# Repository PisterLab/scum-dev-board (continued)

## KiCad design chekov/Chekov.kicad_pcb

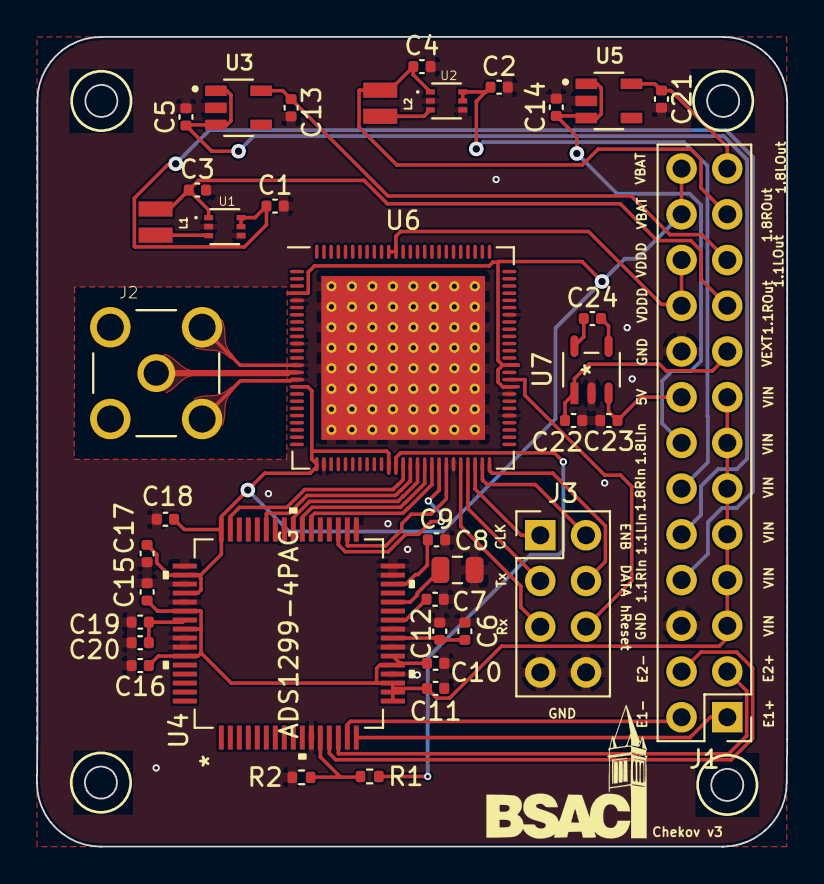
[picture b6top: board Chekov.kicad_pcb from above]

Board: 2 copper layers, 41.7 x 45.0 mm, 38 parts (0 on the bottom side), 43 nets.

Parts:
C1, C2, C3, C4: 10 uF; C_0402_1005Metric
C5, C7, C9, C10, C11, C13, C14, C15, C16, C17, C18, C20, C21: 1u; C_0402_1005Metric
C6, C23: 10u; C_0402_1005Metric
C8: 100u; C_0805_2012Metric
C12, C19, C24: 0.1u; C_0402_1005Metric
C22: 3.3u; C_0402_1005Metric
J1: Conn_02x13_Odd_Even; PinHeader_2x13_P2.54mm_Vertical
J2: CONSMA001-G-CONSMA001-G; LINX_CONSMA001-G
J3: Conn_02x04_Odd_Even; PinHeader_2x04_P2.54mm_Vertical
L1, L2: 2.2 uH; IND_74438343022
R1: 100k; R_0402_1005Metric
R2: 0.82; R_0402_1005Metric
U1: S-85S1AB10-I6T1U; SOFL50P180X50-6N
U2: S-85S1AB18-I6T1U; SOFL50P180X50-6N
U3: TLV70311DBVR; SOT95P280X145-5N
U4: ADS1299-4PAG
U5: TPS7A0518PDBVT; SOT95P280X145-5N
U6: scum3; QFN-100_EP_12x12_Pitch0.4mm_Margin0.25mm
U7: LTC1517ES5-5-TRPBF

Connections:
+VBAT: C17.1, C18.1, J1.24, J1.26, U4.48, U4.50, U4.52, U6.4, U6.17, U6.26, U6.36, U6.59, U6.62
+VDDD: J1.20, J1.22, U6.89, U6.90
+VEXT: C22.1, J1.17, U7.1
+VIN: C10.1, C11.1, C15.1, C16.1, J1.5, J1.7, J1.9, J1.11, J1.13, J1.15, U4.17, U4.18, U4.19, U4.21, U4.22, U4.54, U4.56, U4.59
/5V: C23.1, J1.16, U7.3
/Antenna: J2.1, U6.15
/CLK: J3.1, U6.48
/DATA: J3.4, U6.50
/E1Minus: J1.2, U4.15
/E1Plus: J1.1, U4.16
/E2Minus: J1.4, U4.13
/E2Plus: J1.3, U4.14
/ENB: J3.2, U6.49
/GPIO8: R1.2, U6.37
/GPIO9: U4.47, U6.38
/GPIO10: U4.43, U6.39
/GPIO11: U4.40, U6.40
/GPIO12: U4.39, U6.41
/GPIO13: U4.38, U6.42
/GPIO14: U4.35, U4.36, U6.43
/GPIO15: U4.34, U6.44
/LDO_In1.1: C5.1, J1.10, U3.1, U3.3
/LDO_In1.8: C14.1, J1.14, U5.1, U5.3
/LDO_Out1.1: C13.2, J1.21, U3.5
/LDO_Out1.8: C21.2, J1.25, U5.5
/Reg_In1.1: C1.1, J1.8, U1.5, U1.6
/Reg_In1.8: C2.1, J1.12, U2.5, U2.6
/Reg_Out1.1: C3.1, J1.19, L1.1, U1.1
/Reg_Out1.8: C4.1, J1.23, L2.1, U2.1
/RsRx: J3.5, U6.46
/RsTx: J3.3, U6.47
/hRESET: J3.6, U6.60
/uV: R1.1, R2.2, U4.12
GND: C1.2, C2.2, C3.2, C4.2, C5.2, C6.2, C7.1, C8.1, C9.1, C10.2, C11.2, C12.2, C13.1, C14.2, C15.2, C16.2, C17.2, C18.2, C19.2, C20.2, C21.1, C22.2, C23.2, J1.6, J1.18, J2.S1, J2.S2, J2.S3, J2.S4, J3.7, J3.8, R2.1, U1.2, U1.4, U2.2, U2.4, U3.2, U4.11, U4.20, U4.23, U4.25, U4.31, U4.32, U4.33, U4.41, U4.49, U4.51, U4.53, U4.57, U4.58, U5.2, U6.5, U6.11, U6.14, U6.16, U6.27, U6.45, U6.55, U6.58, U6.69, U6.101, U7.2
unnamed: C7.2, U4.26
unnamed: C8.2, U4.28
unnamed: C9.2, U4.30
unnamed: C6.1, C12.1, U4.24
unnamed: C19.1, C20.1, U4.55
unnamed: C24.1, U7.5
unnamed: C24.2, U7.4
unnamed: L1.2, U1.3
unnamed: L2.2, U2.3

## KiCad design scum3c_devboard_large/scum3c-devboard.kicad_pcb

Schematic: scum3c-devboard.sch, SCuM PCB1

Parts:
C1: 1.5 pF; C_0402_1005Metric
C3, C26, C27: 0.1uF; C_0402_1005Metric
C8, C9, C12, C23, C25, C28: 10 uF; C_0402_1005Metric
E1: 2450AT45A100E; ANT_2450AT45A100E; PARTREV 3.1
H1, H2, H3, H4: MountingHole; MountingHole_2.7mm_M2.5
J1: CONSMA001-G; LINX_CONSMA001-G; PARTREV D
J2: Conn_02x04_Odd_Even; PinHeader_2x04_P2.54mm_Vertical
J3: Conn_02x10_Odd_Even; PinHeader_2x10_P2.54mm_Vertical
J4: Conn_02x13_Odd_Even; PinHeader_2x13_P2.54mm_Vertical
L2, L3, L5: 2.2 uH; L_0402_1005Metric
L4: 3.9 nH; L_0402_1005Metric
U1: Perfboard
U5: ICM-20948; QFN40P300X300X105-24N; PARTREV 1.3
U6: S-85S1AB10-I6T1U; SOFL50P180X50-6N; PARTREV 1.4_00
U7: S-85S1AB15-I6T1U; SOFL50P180X50-6N; PARTREV 1.4_00
U12: S-85S1AB18-I6T1U; SOFL50P180X50-6N; PARTREV 1.4_00
U14, U15: 74AVCH4T245D,118; SOIC127P600X175-16N

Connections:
+1VIN: C25.1, J4.15, L2.1, U6.1 (VOUT)
+15VIN: C28.1, J4.9, L3.1, U7.1 (VOUT)
+TEENSY33: J4.2; also elsewhere on the board
+V18IO: C12.1, J2.7, J4.4, L5.1, U12.1 (VOUT), U14.1, U15.1, U15.2
+V18IO_IMU: C27.1, J2.8, U5.8 (VDDIO)
+VBAT: J4.8, J4.10, J4.11, J4.23; also elsewhere on the board
+VBATSCuM: J4.12; also elsewhere on the board
+VDDD: J4.16, J4.18, J4.19; also elsewhere on the board
+VDDIO: J4.6, J4.13, J4.21, U14.16, U15.16; also elsewhere on the board
+VDDIOSCuM: J4.14; also elsewhere on the board
+VIN: C8.1, C9.1, C23.1, J2.5, J4.1, J4.5, J4.25, U6.5 (VIN), U6.6 (EN), U7.5 (VIN), U7.6 (EN), U12.5 (VIN), U12.6 (EN); also elsewhere on the board
+VIN_IMU: C26.1, J2.6, U5.13 (VDD)
/ADC_IN: J2.3; also elsewhere on the board
/ADC_LDO_OUT: J2.4; also elsewhere on the board
/Boot_Source_Sel: J4.17; also elsewhere on the board
/GPIO0: J3.5; also elsewhere on the board
/GPIO1: J3.2, J3.4, J3.6; also elsewhere on the board
/GPIO2: J3.7; also elsewhere on the board
/GPIO3: J3.8; also elsewhere on the board
/GPIO4: J3.9; also elsewhere on the board
/GPIO5: J3.10; also elsewhere on the board
/GPIO6: J3.11; also elsewhere on the board
/GPIO7: J3.12; also elsewhere on the board
/GPIO8: J3.1, J3.13; also elsewhere on the board
/GPIO9: J3.3, J3.14; also elsewhere on the board
/GPIO10: J3.15; also elsewhere on the board
/GPIO11: J3.16; also elsewhere on the board
/GPIO12: J3.17, U14.11; also elsewhere on the board
/GPIO12_IMU: U5.24 (SDA/SDI), U14.6
/GPIO13: J3.18, U15.12; also elsewhere on the board
/GPIO13_IMU: U5.9 (AD0/SDO), U15.5
/GPIO14: J3.19, U14.12; also elsewhere on the board
/GPIO14_IMU: U5.23 (SCL/SCLK), U14.5
/GPIO15: J3.20, U14.10; also elsewhere on the board
/GPIO15_IMU: U5.22 (~CS), U14.7
/RF_IN: C1.2, J1.1; also elsewhere on the board
GND: C3.1, C8.2, C9.2, C12.2, C23.2, C25.2, C26.2, C27.2, C28.2, J1.S1, J1.S2, J1.S3, J1.S4, J2.1, J2.2, J4.7, J4.20, J4.22, J4.24, J4.26, L4.2, U5.11 (FSYNC), U5.18 (GND), U5.20 (RESV_20), U6.2 (VSS), U6.4 (PVSS), U7.2 (VSS), U7.4 (PVSS), U12.2 (VSS), U12.4 (PVSS), U14.2, U14.3, U14.8, U14.9, U14.14, U14.15, U15.3, U15.8, U15.9, U15.14, U15.15; also elsewhere on the board
unnamed: C1.1, E1.1, L4.1
unnamed: C3.2, U5.10 (REGOUT)
unnamed: L2.2, U6.3 (SW)
unnamed: L3.2, U7.3 (SW)
unnamed: L5.2, U12.3 (SW)
unnamed: U1.11, U1.21, U1.31, U1.41
unnamed: U1.12, U1.22, U1.32, U1.42
unnamed: U1.13, U1.23, U1.33, U1.43
unnamed: U1.14, U1.24, U1.34, U1.44
unnamed: U1.15, U1.25, U1.35, U1.45
unnamed: U1.16, U1.26, U1.36, U1.46
unnamed: U1.17, U1.27, U1.37, U1.47
unnamed: U1.18, U1.28, U1.38, U1.48

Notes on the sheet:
IMU
Perfboard and Mounting Holes
Power Flags
UART
SCuM
Antenna
Teensy Connectors
DC-DC Converters
GPIO
Voltage Pins
ADC/IMU Pins
IMU Level Shifters

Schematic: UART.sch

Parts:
C2: 10nF; C_0402_1005Metric
C4: 4.7uF; C_0402_1005Metric
C5, C6, C7: 0.1uF; C_0402_1005Metric
C10, C11: 47pF; C_0402_1005Metric
C13: C; C_0402_1005Metric
D1, D2: LED; LED_0402_1005Metric
J5: 1050170001; MOLEX_1050170001; PARTREV F
J9: Conn_02x03_Odd_Even; PinHeader_2x03_P2.54mm_Vertical
L1: HZ0805E601R-10; L_0805_2012Metric; Manufacturer_Part_Number HZ0805E601R-10
R1, R4: 270; R_0402_1005Metric
R2, R3: 27; R_0402_1005Metric
U2: FT231XS-U; SSOP-20_3.9x8.7mm_P0.635mm; Manufacturer_Part_Number FT231XS-U; Mouser Part Number 895-FT231XS-U
U3, U4: 74AVC1T45GS-Q100H; 74LVC1G3157GS132; Manufacturer_Part_Number 74AVC1T45GS,132; Mouser Part Number 771-74AVC1T45GS132

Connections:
+VBAT: U3.1 (VCCA); also elsewhere on the board
+VDDIO: U4.1 (VCCA), U4.5 (DIR); also elsewhere on the board
+VIN: U3.6 (VCCB), U4.6 (VCCB); also elsewhere on the board
+VUSB: C4.1, C7.1, L1.2, U2.15 (VCC)
/RsRx: U3.3 (A); also elsewhere on the board
/RsTx: U4.3 (A); also elsewhere on the board
/Rx33: J9.2; also elsewhere on the board
/Tx33: J9.1; also elsewhere on the board
/UART/D_N: C11.2, J5.2, R3.2
/UART/D_P: C10.1, J5.3, R2.1
/UART/RsRx33: J9.4, U3.4 (B)
/UART/RsRx33USB: J9.6, U2.20 (TXD)
/UART/RsTx33: J9.3, U4.4 (B)
/UART/RsTx33USB: J9.5, U2.4 (RXD)
GND: C2.2, C4.2, C5.2, C6.2, C7.2, C10.2, C11.1, C13.2, J5.5, U2.6 (GND_1), U2.16 (GND_2), U3.2 (GND), U3.5 (DIR), U4.2 (GND); also elsewhere on the board
unnamed: C2.1, J5.1, L1.1
unnamed: C13.1, J5.SH1, J5.SH2, J5.SH3, J5.SH4, J5.SH5, J5.SH6, J5.SH7, J5.SH8
unnamed: D1.1 (K), U2.10 (CBUS2)
unnamed: D1.2 (A), R1.2
unnamed: D2.1 (K), U2.17 (CBUS1)
unnamed: D2.2 (A), R4.2
unnamed: R2.2, U2.11 (USBDP)
unnamed: R3.1, U2.12 (USBDM)

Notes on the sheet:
USB to UART
USB
UART Level Shifters
Jumpers

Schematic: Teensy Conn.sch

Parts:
J6: Conn_01x24; PinSocket_1x24_P2.54mm_Vertical
U9, U10, U11, U13: 74AVCH4T245D,118; SOIC127P600X175-16N

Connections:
+TEENSY33: J6.3; also elsewhere on the board
+VBAT: U9.1, U10.1, U11.1, U13.1, U13.2; also elsewhere on the board
+VIN: U9.16, U10.16, U11.16, U13.16; also elsewhere on the board
/3WB_CLK: U11.6; also elsewhere on the board
/3WB_DATA: U11.4; also elsewhere on the board
/3WB_ENB: U11.5; also elsewhere on the board
/Clock: U10.6; also elsewhere on the board
/GPIO0: J6.11; also elsewhere on the board
/GPO_ZERO: U10.7; also elsewhere on the board
/Rx33: J6.5, J6.23; also elsewhere on the board
/Teensy Connections/3WB_CLK33: J6.8, U11.11
/Teensy Connections/3WB_DATA33: J6.10, U11.13
/Teensy Connections/3WB_ENB33: J6.9, U11.12
/Teensy Connections/Clock33: J6.13, U10.11
/Teensy Connections/GPO_ZERO33: J6.12, U10.10
/Teensy Connections/aLOAD33: J6.19, U9.12
/Teensy Connections/aPHI33: J6.18, U9.11
/Teensy Connections/aPHIb33: J6.14, U10.12
/Teensy Connections/aSCANIN33: J6.20, U9.13
/Teensy Connections/aSCANOUT33: J6.16, J6.21, U13.13
/Teensy Connections/aSCSEL33: J6.17, J6.22, U9.10
/Teensy Connections/hReset33: J6.7, U11.10
/Tx33: J6.4, J6.24; also elsewhere on the board
/aLOAD: U9.5; also elsewhere on the board
/aPHI: U9.6; also elsewhere on the board
/aPHIb: U10.5; also elsewhere on the board
/aSCANIN: U9.4; also elsewhere on the board
/aSCANOUT: U13.4; also elsewhere on the board
/aSCSEL: U9.7; also elsewhere on the board
/hReset: U11.7; also elsewhere on the board
GND: J6.6, J6.15, U9.2, U9.3, U9.8, U9.9, U9.14, U9.15, U10.2, U10.3, U10.8, U10.9, U10.14, U10.15, U11.2, U11.3, U11.8, U11.9, U11.14, U11.15, U13.3, U13.8, U13.9, U13.14, U13.15; also elsewhere on the board

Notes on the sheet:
Teensy/nRF Connector
Level Shifters

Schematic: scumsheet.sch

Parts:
U8: scum3; QFN-100_EP_12x12_Pitch0.4mm

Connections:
+VBATSCuM: U8.4 (VBAT), U8.17 (VBAT), U8.26 (VBAT), U8.59 (VBAT), U8.62 (VBAT); also elsewhere on the board
+VDDD: U8.89 (VDDD), U8.90 (VDDD); also elsewhere on the board
+VDDIOSCuM: U8.36 (VDDIO); also elsewhere on the board
/3WB_CLK: U8.48 (3WB_CLK); also elsewhere on the board
/3WB_DATA: U8.50 (3WB_DATA); also elsewhere on the board
/3WB_ENB: U8.49 (3WB_ENB); also elsewhere on the board
/ADC_IN: U8.54 (SENSOR_EXT_IN); also elsewhere on the board
/ADC_LDO_OUT: U8.53 (SENSOR_LDO_OUTPUT); also elsewhere on the board
/Boot_Source_Sel: U8.61 (BOOT_SOURCE_SELECT); also elsewhere on the board
/Clock: U8.56 (LF_CLK_EXT_IN); also elsewhere on the board
/GPIO0: U8.28 (GPIO0); also elsewhere on the board
/GPIO1: U8.29 (GPIO1); also elsewhere on the board
/GPIO2: U8.30 (GPIO2); also elsewhere on the board
/GPIO3: U8.31 (GPIO3); also elsewhere on the board
/GPIO4: U8.32 (GPIO4); also elsewhere on the board
/GPIO5: U8.33 (GPIO5); also elsewhere on the board
/GPIO6: U8.34 (GPIO6); also elsewhere on the board
/GPIO7: U8.35 (GPIO7); also elsewhere on the board
/GPIO8: U8.37 (GPIO8); also elsewhere on the board
/GPIO9: U8.38 (GPIO9); also elsewhere on the board
/GPIO10: U8.39 (GPIO10); also elsewhere on the board
/GPIO11: U8.40 (GPIO11); also elsewhere on the board
/GPIO12: U8.41 (GPIO12); also elsewhere on the board
/GPIO13: U8.42 (GPIO13); also elsewhere on the board
/GPIO14: U8.43 (GPIO14); also elsewhere on the board
/GPIO15: U8.44 (GPIO15); also elsewhere on the board
/GPO_ZERO: U8.57 (GPO_ZERO); also elsewhere on the board
/RF_IN: U8.15 (RF_IN); also elsewhere on the board
/RsRx: U8.47 (RSRX); also elsewhere on the board
/RsTx: U8.46 (RSTX); also elsewhere on the board
/aLOAD: U8.66 (ASC_LOAD); also elsewhere on the board
/aPHI: U8.64 (ASC_PHI1); also elsewhere on the board
/aPHIb: U8.63 (ASC_PHI2); also elsewhere on the board
/aSCANIN: U8.67 (ASC_IN); also elsewhere on the board
/aSCANOUT: U8.65 (ASC_OUT); also elsewhere on the board
/aSCSEL: U8.68 (ASC_EXT_OVERRIDE); also elsewhere on the board
/hReset: U8.60 (HARD_RESET); also elsewhere on the board
GND: U8.5 (GND), U8.11 (GND), U8.14 (RF_GND), U8.16 (RF_GND), U8.27 (GND), U8.45 (GND), U8.55 (GND), U8.58 (GND), U8.69 (GND), U8.101 (GND); also elsewhere on the board

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
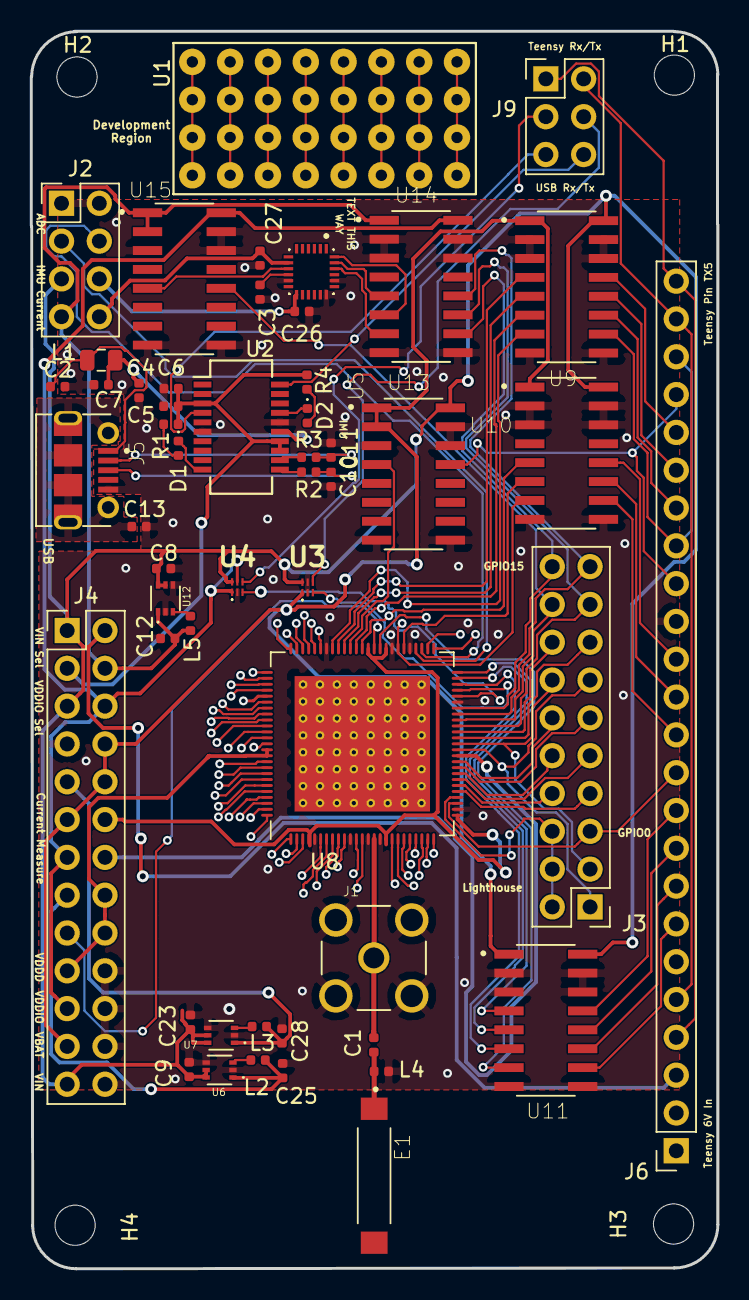
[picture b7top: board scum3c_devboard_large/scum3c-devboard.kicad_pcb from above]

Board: 2 copper layers, 46.1 x 83.1 mm, 56 parts (0 on the bottom side), 94 nets.

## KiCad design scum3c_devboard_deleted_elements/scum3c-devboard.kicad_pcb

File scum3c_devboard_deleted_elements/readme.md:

### Updates 2020.12.05
- removed zener diode
- added GPIOs 8, 9, 10
- added ground connections near GPIO
- added labels
- moved passives around
- added ADC pins

### Updates 2020.12.02
- Replaced antenna header with VDDD
- Kept LED
- 0-80 standoffs
- 0.1” -> 0.05” headers
- Removed GPIO 8-15 pins

### Updates 2020.10.07
- 30mm x 30 mm
- holes for standoffs
- SR521SW battery clip
- IMU
- GPIO, 3WB, UART, VBAT, VDDIO pins
- 1.8 V Zener diode for voltage protection
- LED programming indicator

### Updates 2021.01.15
- Added missing BOOT_SOURCE_SEL header

## useful specs
Use 0-80 standoffs. 1.6 mm diameter hole, 3.2 mm diameter clearance. https://www.4pcb.com/pcb-design-specifications/

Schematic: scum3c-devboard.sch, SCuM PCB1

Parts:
BT1: Battery_Cell; 2986
C25, C26, C27: 0.1uF; C_0402_1005Metric
J1: Conn_02x04_Odd_Even; PinHeader_2x04_P2.54mm_Vertical
J2, J5: Conn_01x02; PinHeader_1x02_P2.54mm_Vertical
J3: Conn_02x10_Odd_Even; PinHeader_2x10_P2.54mm_Vertical
J4: Conn_02x08_Odd_Even; PinHeader_2x08_P2.54mm_Vertical
JC1: Conn_01x01; PinHeader_1x01_P2.54mm_Vertical
U9AB1: ICM-20948; InvenSense_QFN-24_3x3mm_P0.4mm

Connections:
+VBAT: BT1.1 (+), J1.5, J4.1; also elsewhere on the board
+VDDD: J4.5, J4.7; also elsewhere on the board
+VDDIO: J1.1, J1.3, J1.6, J4.3; also elsewhere on the board
/3WB_CLK: J4.14; also elsewhere on the board
/3WB_DATA: J4.10; also elsewhere on the board
/3WB_ENB: J4.12; also elsewhere on the board
/ANTENNA: JC1.1; also elsewhere on the board
/BOOT_SOURCE_SEL: J4.8; also elsewhere on the board
/GPIO0: J3.1; also elsewhere on the board
/GPIO1: J2.1, J2.2, J3.3; also elsewhere on the board
/GPIO2: J3.5; also elsewhere on the board
/GPIO3: J3.7; also elsewhere on the board
/GPIO4: J3.9; also elsewhere on the board
/GPIO5: J3.11; also elsewhere on the board
/GPIO6: J3.13; also elsewhere on the board
/GPIO7: J3.15; also elsewhere on the board
/GPIO8: J3.2; also elsewhere on the board
/GPIO9: J3.4; also elsewhere on the board
/GPIO10: J3.6; also elsewhere on the board
/GPIO11: J3.8; also elsewhere on the board
/GPIO12: J3.10, U9AB1.24 (SDA/SDI); also elsewhere on the board
/GPIO13: J3.12, U9AB1.9 (SDO/AD0); also elsewhere on the board
/GPIO14: J3.14, U9AB1.23 (SCL/SCLK); also elsewhere on the board
/GPIO15: J3.16, U9AB1.22 (~CS); also elsewhere on the board
/GPO_ZERO: J5.2; also elsewhere on the board
/HARD_RESET: J4.16; also elsewhere on the board
/IMU_VDD: C26.1, J1.2, U9AB1.13 (VDD)
/IMU_VDDIO: C27.1, J1.4, U9AB1.8 (VDDIO)
/RsRx: J4.13; also elsewhere on the board
/RsTx: J4.15; also elsewhere on the board
/SENSOR_EXT_IN: J4.9; also elsewhere on the board
/SENSOR_LDO_OUTPUT: J4.11; also elsewhere on the board
GND: BT1.2 (-), C25.2, C26.2, C27.2, J1.7, J1.8, J3.17, J3.18, J3.19, J3.20, J4.2, J4.4, J4.6, J5.1, U9AB1.11 (FSYNC), U9AB1.18 (GND), U9AB1.20 (GND); also elsewhere on the board
unnamed: C25.1, U9AB1.10 (REGOUT)

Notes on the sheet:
Invensense MPU-9250 and ICM-20948 are pin compatible When using MPU-9250, VDDIO can be 1.71V-3.3V When using ICM-20948, VDDIO can be 1.71V-1.95V Easiest way to use ICM-20948 is to replace 1.5V VBAT LDO with 1.8V and set VDDIO=VBAT
SCuM
IMU
External Connections
Battery
McCoy PCB v1.1

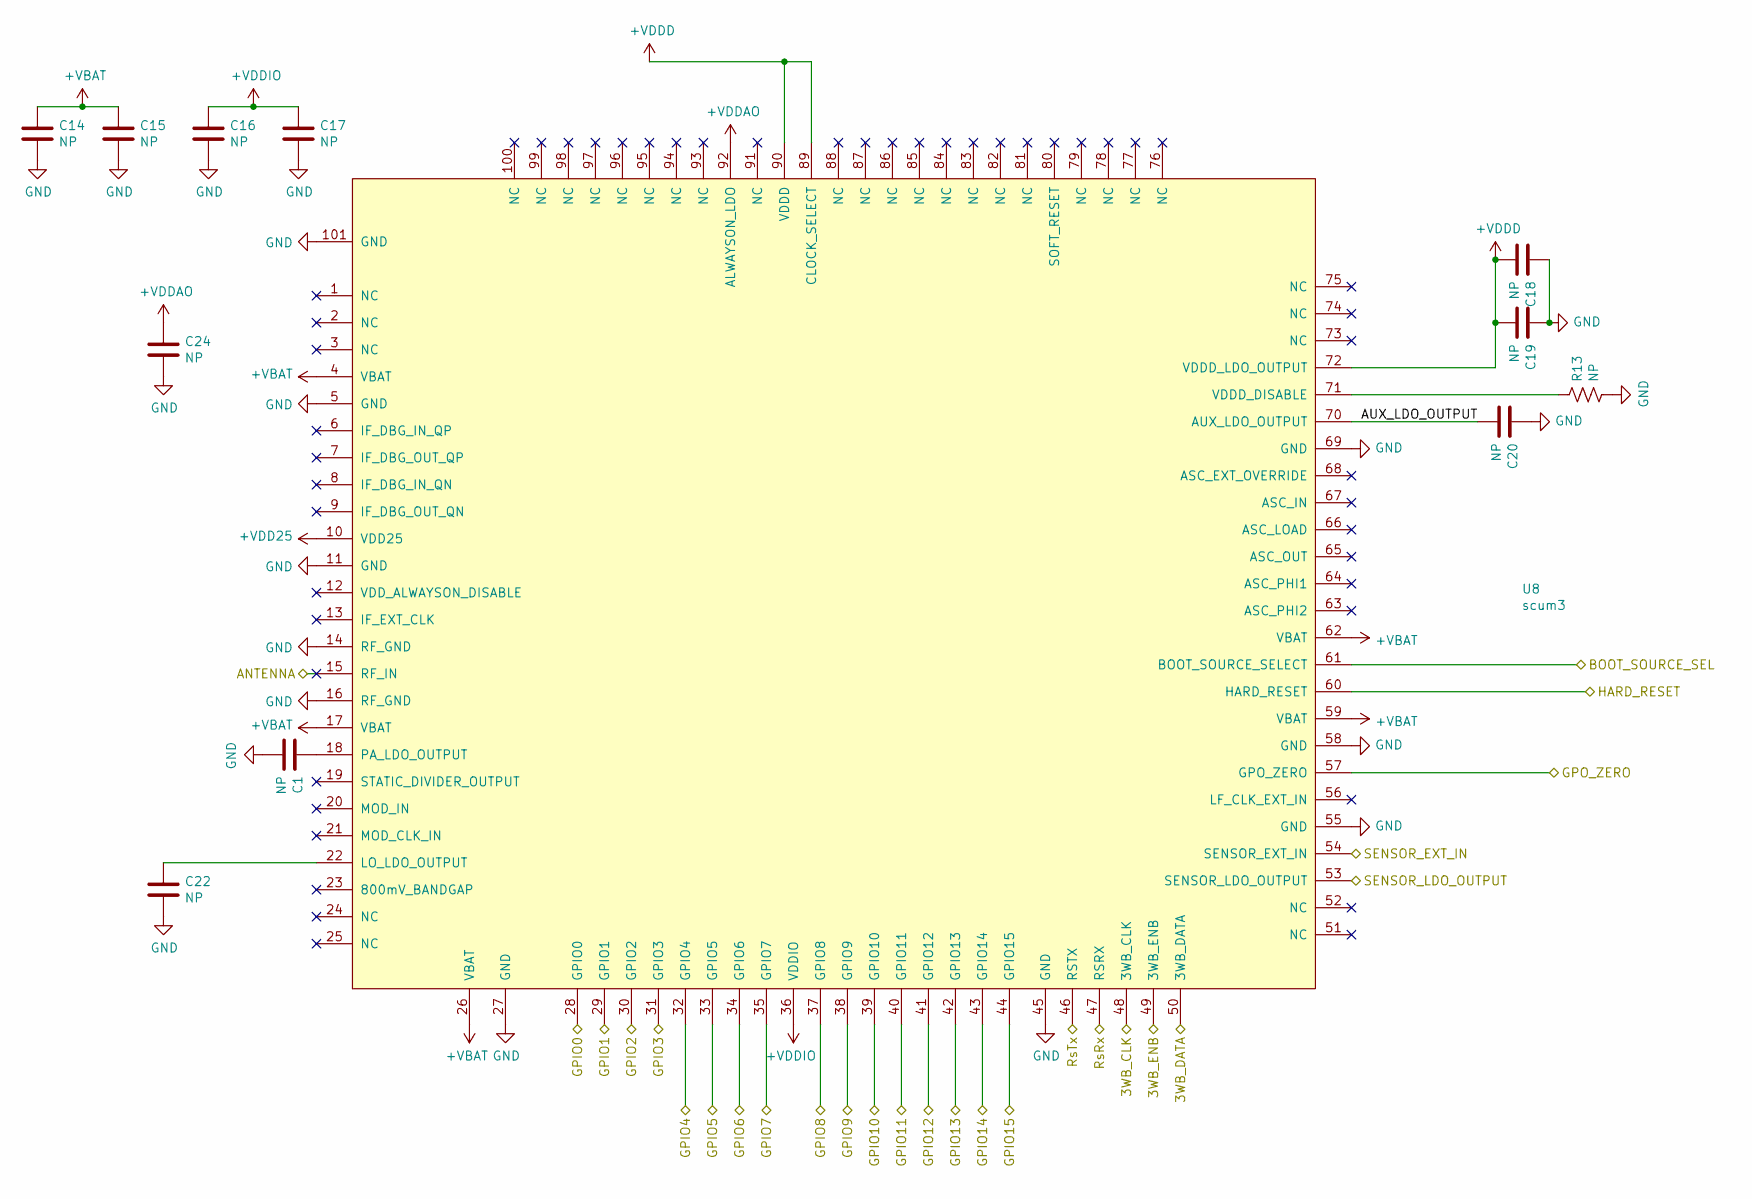
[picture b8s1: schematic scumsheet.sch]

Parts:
C1, C14, C15, C16, C17, C18, C19, C20, C22, C24: NP; C_0402_1005Metric
R13: NP; R_0402_1005Metric
U8: scum3; QFN-100_EP_12x12_Pitch0.4mm_Margin0.25mm

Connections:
+VBAT: C14.1, C15.1, U8.4 (VBAT), U8.17 (VBAT), U8.26 (VBAT), U8.59 (VBAT), U8.62 (VBAT); also elsewhere on the board
+VDDAO: C24.1, U8.92 (ALWAYSON_LDO)
+VDDD: C18.2, C19.2, U8.72 (VDDD_LDO_OUTPUT), U8.89 (CLOCK_SELECT), U8.90 (VDDD); also elsewhere on the board
+VDDIO: C16.1, C17.1, U8.36 (VDDIO); also elsewhere on the board
/3WB_CLK: U8.48 (3WB_CLK); also elsewhere on the board
/3WB_DATA: U8.50 (3WB_DATA); also elsewhere on the board
/3WB_ENB: U8.49 (3WB_ENB); also elsewhere on the board
/ANTENNA: U8.15 (RF_IN); also elsewhere on the board
/BOOT_SOURCE_SEL: U8.61 (BOOT_SOURCE_SELECT); also elsewhere on the board
/GPIO0: U8.28 (GPIO0); also elsewhere on the board
/GPIO1: U8.29 (GPIO1); also elsewhere on the board
/GPIO2: U8.30 (GPIO2); also elsewhere on the board
/GPIO3: U8.31 (GPIO3); also elsewhere on the board
/GPIO4: U8.32 (GPIO4); also elsewhere on the board
/GPIO5: U8.33 (GPIO5); also elsewhere on the board
/GPIO6: U8.34 (GPIO6); also elsewhere on the board
/GPIO7: U8.35 (GPIO7); also elsewhere on the board
/GPIO8: U8.37 (GPIO8); also elsewhere on the board
/GPIO9: U8.38 (GPIO9); also elsewhere on the board
/GPIO10: U8.39 (GPIO10); also elsewhere on the board
/GPIO11: U8.40 (GPIO11); also elsewhere on the board
/GPIO12: U8.41 (GPIO12); also elsewhere on the board
/GPIO13: U8.42 (GPIO13); also elsewhere on the board
/GPIO14: U8.43 (GPIO14); also elsewhere on the board
/GPIO15: U8.44 (GPIO15); also elsewhere on the board
/GPO_ZERO: U8.57 (GPO_ZERO); also elsewhere on the board
/HARD_RESET: U8.60 (HARD_RESET); also elsewhere on the board
/RsRx: U8.47 (RSRX); also elsewhere on the board
/RsTx: U8.46 (RSTX); also elsewhere on the board
/SENSOR_EXT_IN: U8.54 (SENSOR_EXT_IN); also elsewhere on the board
/SENSOR_LDO_OUTPUT: U8.53 (SENSOR_LDO_OUTPUT); also elsewhere on the board
/scumsheet/AUX_LDO_OUTPUT: C20.2, U8.70 (AUX_LDO_OUTPUT)
GND: C1.2, C14.2, C15.2, C16.2, C17.2, C18.1, C19.1, C20.1, C22.2, C24.2, R13.2, U8.5 (GND), U8.11 (GND), U8.14 (RF_GND), U8.16 (RF_GND), U8.27 (GND), U8.45 (GND), U8.55 (GND), U8.58 (GND), U8.69 (GND), U8.101 (GND); also elsewhere on the board
unnamed: C1.1, U8.18 (PA_LDO_OUTPUT)
unnamed: C22.1, U8.22 (LO_LDO_OUTPUT)
unnamed: R13.1, U8.71 (VDDD_DISABLE)

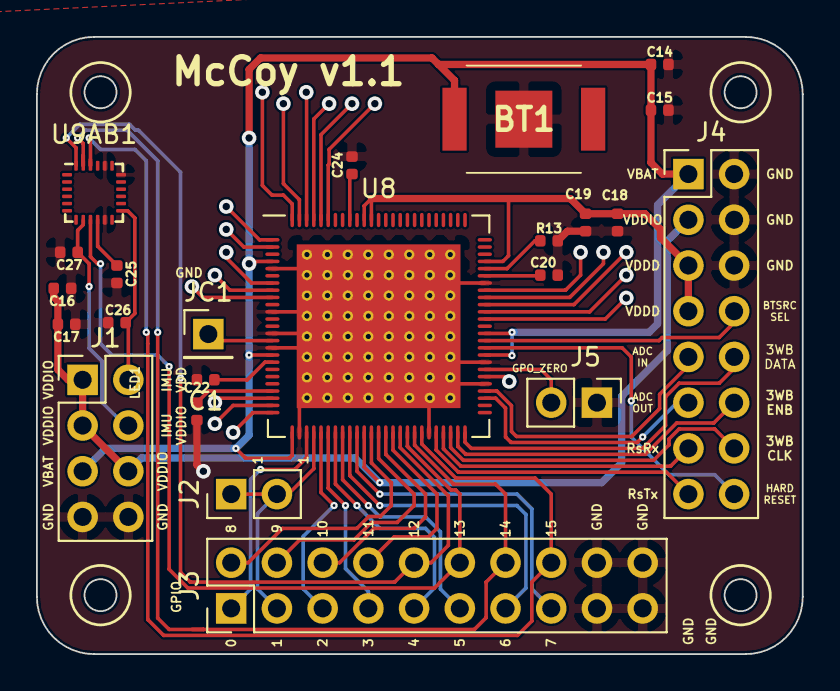
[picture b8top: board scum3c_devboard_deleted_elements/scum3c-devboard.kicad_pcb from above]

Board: 2 copper layers, 42.5 x 34.3 mm, 23 parts (0 on the bottom side), 39 nets.

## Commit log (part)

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2020-09-16 renamed
2020-09-16 untracked everything gitignored filed
2020-10-05 added zener diode voltage protection
2020-10-05 added LED
2020-10-05 ground plane
2020-10-07 shrink to 30mm square
2020-10-07 prerouting
2020-10-07 finished traces hopefully
2020-12-01 notes on why things are the way they are
2020-12-01 changed header size
2020-12-01 replaced headers with smaller ones
2020-12-01 changed to mixed signals on front and back
2020-12-01 routed traces
2020-12-02 copy-pasted over large board
2020-12-02 made ground fill solid instead of thermal
2020-12-05 added ADC pins
2020-12-05 deleted zener diode
2020-12-05 added gpio 8 9 10 and gnd pins
2020-12-06 flipped around gpio headers
2020-12-06 added scum footprint settings
2020-12-06 created new QFN for scum just in case other one bugged
2020-12-06 added gpio8-10
2020-12-06 Revert "added gpio8-10"
    This reverts commit daf7284f57cd8196d10e3621e3573955ecb68719.
2020-12-06 deleted tracks
2020-12-06 placed components
2020-12-06 placed vbat
2020-12-06 added layer 1 ground zone
2020-12-06 replaced gpio8-10
2020-12-06 placed scum contact tracks
2020-12-06 placed led ground
2020-12-06 untraced ground pins
2020-12-06 "J1"->"JA1"
2020-12-06 refilled ground
2020-12-06 Revert "refilled ground"
    This reverts commit 937a25d859cc705142fc3d9099eb29337f2ecc38.
2020-12-06 redid ground layer
2020-12-06 cleaned vbat a bit
2020-12-06 saved updated 3d renders
2020-12-06 saved schematic pdf
2020-12-06 added log
2020-12-06 moved into folder
2020-12-06 Revert "moved into folder"
    This reverts commit 9d27eba87dcf45b49149a225428457ea5dd9b7b4.
2020-12-06 Revert "given friendly names"
    This reverts commit 38134d1d0f401e9393679a883172811fa3646ba9.
2020-12-06 moved into pics folder
2020-12-06 added images
2020-12-07 described versions
2020-12-07 described link
2021-01-15 added missing BOOT_SOURCE_SEL header
2021-01-20 made gerber files
2021-01-20 fixed typo in filename
2021-01-22 replaced level shifters and other changes
2021-01-23 connected IMU
2021-01-23 placed smds
2021-01-23 put in 2 rows for gpio
2021-01-23 placed labels
2021-01-23 updated preview images
2021-01-23 connected missing ground
2021-01-23 noconn on imu pin 12
2021-01-24 zipped gerber files
2021-01-27 generated bom
2021-01-27 front image of 3d render
2021-02-06 drew bond diagram
2021-02-09 [ll] cob info and qfn info, the former waiting on antenna results
2021-02-12 Added antenna pin.
    Also:
    - added antenna pin to SCuM (not ideal, but it's there)
    - increased screw hole size slightly for better M1.6 screw fit
    - rounded board corners
    - fixed part labels
    - added name "McCoy" and logo
2021-02-12 updated board images
2021-02-13 Bond diagram for large board
2021-02-17 Revert "Bond diagram for large board"
    This reverts commit 91bc62fe396b7a875cf0b3036525612d33b127e8.
2021-02-17 Revert "added pictures of board with antenna pin"
    This reverts commit 066ada8f295b33980781327265b6d91000a7e986.
2021-02-17 Revert "Added antenna pin."
    This reverts commit 8df6496cb9b2ea83d1615ae89a231b84e6049366.
2021-02-18 clarified two labels on schematic
2021-03-09 With through-hole antenna
2021-04-05 Added annotated schematic for McCoy
2021-04-05 Added bond diagram for essential bonds testing board
2021-04-09 ensuring large board up to date with master
2021-04-12 Suggested changes
2021-04-12 replaced footprints
2021-04-12 connected gpios
2021-04-12 routed vddio
2021-04-12 routed everything? except imu
2021-04-12 changed drc rules
2021-04-12 added a bunch of vias that probably won't work
2021-04-12 labaled components
2021-04-13 routed all traces
2021-04-13 added grounds
2021-04-14 added some through vias
2021-04-14 fixed a label
2021-04-14 updated pictures
2021-04-14 created custom battery clip
2021-04-14 added a datasheet
2021-04-14 renamed batter cell to battery clip
2021-04-14 placed bsac logo
2021-04-14 saved correct schematic image
2021-04-16 added a bunch of vias
2021-04-16 Create bom_csv
2021-04-16 generated gerber files
2021-04-16 made new gerber zip
2021-04-25 removed old tracks
2021-04-26 routed some gpios
2021-04-26 routed gpios
2021-04-26 moved the logos and labels
2021-04-26 saved pictures
2021-04-26 changed version number
2021-04-26 added back labels
2021-04-26 created bom
2021-04-26 redid gerber with some silkscreen adjusts
2021-04-26 got pictures
2021-04-26 switching computers
2021-04-28 updated with review material
2021-04-28 label a hole
2021-04-28 updated labels
2021-04-28 generated new gerber
2021-04-28 added gerbers
2021-04-29 added some labels for clarity
2021-04-29 swapped around GPIO 2 and 3 for nrf
2021-05-10 Added updated bonding diagrams for self testing for both boards
2021-05-11 Updated description of mccoy
2021-05-11 Removed old standoffs note
2021-06-14 Revert "imported regulator"
    This reverts commit 21acbcdedd9fb6581e4eeac513dd30e56fc47c9f.
2021-06-16 added a regulator to layout
2021-06-25 added TPS60500 regulator
2021-06-25 removed old footprints
2021-06-25 cleared all tracks
2021-06-25 moved some footprints
2021-06-25 added voltage divider to nrf_vddd
2021-06-30 added some starter traces, removed old via size
2021-06-30 headers on the left
2021-06-30 connected all nets
2021-06-30 new images
2021-08-03 Added wirebond diagram for mccoy
2021-08-24 added some dimension
2021-08-26 created external battery pin
2021-08-26 added larger left header set
2021-08-26 external battery pin
2021-08-26 created regulator voltage symbols
2021-08-26 Revert "created regulator voltage symbols"
    This reverts commit 2e3631360fcf3ed4d9fbef1533d95bcecbf0b44b.
2021-08-26 regulator voltage pins
2021-08-26 added vddd nrf
2021-08-26 created regulator symbol
2021-08-27 created snt-6a footprint
2021-08-27 added regulators to pcb
2021-08-27 corrected pin labels on regulator
2021-08-27 added courtyard
2021-08-27 routed regulator traces
2021-08-27 moved north pins down a bit
2021-08-27 numbered reg caps
2021-08-27 added caps to bom
2021-08-27 started adding labels
2021-08-27 finished labels
2021-08-27 brought bom up to date
2021-08-27 added 0 ohm resistor footprint between pins 89 and 90
2021-08-28 added sum total
2021-08-28 labeled R4
2021-08-28 generated gerber files for mccoy 3.0
2021-08-28 added OOS label to IMU :(
2021-08-31 added LDOS
2021-08-31 adjusted LDOs so they don't overlap
2021-09-03 added CR2477 battery holder
2021-09-03 added 1.1V reg input
2021-09-03 added labels
2021-09-03 checkout mccoy v2
2021-09-03 created folders for regulator and ldo versions
2021-09-03 added 3d model for battery holder
2021-09-03 updated ldo with 3d model from reg
2021-09-03 connected ldo traces
2021-09-03 checked out ldo version from ldo branch
2021-09-03 updated sulu bom
2021-09-03 deleted mccoy 3 gerbers
2021-09-03 moved panelized to its own folder
2021-09-03 generated gerber files - no solder paste
2021-09-03 added a dimension for the joint
2021-09-03 hid a bunch of layers
2021-09-03 removed tab to separate panels
2021-09-03 generated gerber for 2 panels without tab
2021-09-03 added dimensions and generated gerber for 8x6 panel
2021-09-04 moved parts out of the way of sma
2021-09-05 rearranged some architecture
2021-09-05 connected most things except breakouts
2021-09-05 Revert "rearranged some architecture"
    This reverts commit c12dfdee068bb4749b85b6faf8935c1bd7e1da4a.
2021-09-05 added keepout to antenna
2021-09-06 connected most things on the north headers
2021-09-11 removed vbat under antenna
2021-09-11 moved battery north a little
2021-09-11 changed front ground to exclude antenna region
2021-09-11 added gnd connections to antenna
2021-09-11 put ldos on pcb
2021-09-11 moved labels for LDOOs
2021-09-11 turned on all layers
2021-09-11 fill zones
2021-09-11 placed on grid
2021-09-11 deleted old gerber files
2021-09-11 added dimensions
2021-09-11 aligned to 100 mil grid
2021-09-11 renamed gerber folders to match type of sulu
2021-09-12 did half the array
2021-09-13 2x1 array. hopefully they can copy it about
2021-09-13 deleted a dimenion
2021-09-14 added alignment holes to solder paste layer
2021-09-14 added alignment holes
2021-09-15 updated boms with antenna
2021-09-19 updated with parts that got ordered
2021-10-10 put inductor on reg bom
2021-11-03 corrected swapped inductors
2021-11-15 switched out dc-dc converter footprints to recommended components
2021-11-15 adjusted a label a touch
2021-11-15 updated pictures to current version
2021-11-20 changed 2x5 to 1x10 nrf header
2021-11-20 adjusted standoff holes
2021-11-20 moved labels for nrf header
2021-11-21 brought images up to date with single row nrf
2021-11-21 deleted old gerbers
2021-11-21 nrf header change
2021-11-21 table for mapping nRF to
2021-11-21 noted dots
2021-11-21 dots on front
2021-11-21 fixed table formatting
2021-11-23 flipped around the nrf header
2021-11-23 unoverlapped labels
2021-11-23 gnd move
2021-11-24 swapped around table of pins between sulu and nrf
2021-11-24 moved a trace away from vias
2021-12-10 updated to recommended caps
2021-12-10 put bom in zip
2021-12-10 bold schematic labels
2021-12-10 changed schematic name
2021-12-11 added headers to bom
2021-12-12 generated centroids
2022-08-30 Added thermal relief to connector TH pads
2022-08-30 Version bumped silkscreen & schematic to V2.1
2022-08-31 Added thermal relief to SMA connector and SCUM package footprint
2022-09-04 Sulu-ads1299 schematic largely completed
2022-09-05 Sulu-ads1299 migrating libs and fixing ERC
2022-09-05 Sulu-ads1299 started layout & imported shared footprints
2022-09-06 Sulu-ads1299 finalized floorplan, began routing, updated schematic
2022-09-08 Sulu-ads1299 layout nearly complete
2022-09-09 Generated Sulu v2.1 gerbers, drill files & updated BOM
2022-09-09 Generated SMT component placements
2022-09-14 Sulu-ADS1299 completed silkscreen
2022-09-14 Sulu-ads1299 switched to backside female connectors
2022-09-22 Upated schematic and layout.
2022-09-22 Sulu-ADS1299 10uF DCDC output decap, BoM, and bigger C20 footprint
2022-09-23 Added sulu-ads1299 part list (not BOM)
2022-09-28 Completed Sulu-ads1299 BOM
2022-09-28 Sulu-ads1299 3.3uF differential filter caps in bom
2022-09-29 Sulu-ads1299 update pcb from sch
2022-09-29 Sulu-ads1299 added thermal relief to TH footprints, exported gerbers and DFs
2022-10-27 Updated Sulu bom and component pos files for assembly
2022-10-27 Updated Sulu-ADS1299 bom and component files for assembly
2023-03-27 Sulu-ADS1299 added PDF of full schematic
2023-05-19 Sulu-ADS1299 started revision 2, added Molex libs, Banana for scale
2023-05-21 Updated sulu-ads1299 rev2 layout and schematic
2023-05-23 Sulu-ADS1299 components placed, new antenna, some routing
2023-05-24 Sulu-ADS1299 rev2 most of the routing done
2023-05-25 Silkscreen cleaned, reduced TP footprint #, post design review
2023-05-25 Sulu-ADS1299 rev2 commit before changing 1.1V regulator
2023-06-01 Final submitted layout, gerbers, drill files, bom, and cpl
2023-06-02 Added Molex to std pitch connector/programmer board
2023-06-23 Sulu-ADS1299 Rev 3 improved routing surrounding QFN
2023-07-13 Sulu-ADS1299 rev 3 fixed gpios, debug connector, two regulators
2023-07-14 Sulu-ADS1299 and connector board layout+sch progress
2023-07-20 Sulu-ADS1299 mosfet input protection circuit
2023-07-20 Fixed DRC rules for JLC PCB
2023-07-20 Completed silkscreen for Rev. 3
2023-07-21 Initial attempt at Sulu board for SmartStake
2023-07-21 Modify schematics after review
2023-07-24 Finished layout after review
2023-07-27 SCuM Programmer Rev. 2, submitted for fab
2023-07-27 Folder rename sulu-programmer -> scum-programmer for consistency
2023-08-02 Final touches
2024-01-25 Sulu-ADS1299-rev3 progress
2024-01-25 Sulu-ADS1299 rev3 layout and schematic progress
2024-01-27 Sulu-ADS1299 rev3 nearly done
2024-02-05 Finished Sulu-ADS1299 Rev 3 layout
2024-02-09 Sulu-ADS1299 rev3 matching network, BOM
2024-02-10 Final submitted Sulu-ADS1299 rev 3
2024-02-19 Sulu-ADS1299 rev3 updated BOM
2024-07-31 Add JLCPCB LCSC part numbers
2024-07-31 Replace DC-DC regulators with LDO regulators
2024-07-31 Add ground stitching vias
2025-04-04 Add Raspberry Pi Pico breakout board
2025-04-04 Add Raspberry Pi Pico W breakout board
2025-04-09 Fix mounting hole positions
2025-04-09 Ignore KiCad backups
